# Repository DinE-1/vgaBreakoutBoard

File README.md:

# VGA Breakout

A KiCad PCB breakout board providing easy access to VGA connector pins.

# Pictures

## Front

## Back

## License

Copyright (c) 2026 DinE-1

Licensed under the CERN Open Hardware Licence Version 2 - Permissive (CERN-OHL-P v2).

See the LICENSE file for details.

## Disclaimer

This design is provided as-is, without warranty of any kind.

Verify electrical compatibility and suitability for your application before manufacture or use. DinE-1 assumes no responsibility for damage, malfunction, data loss, or other consequences resulting from use of this design.

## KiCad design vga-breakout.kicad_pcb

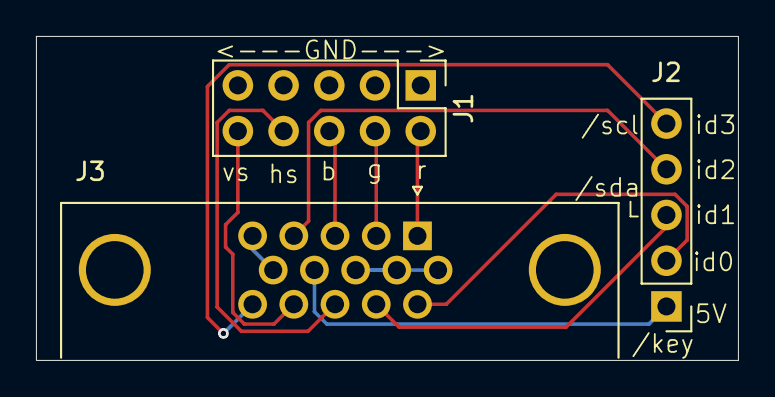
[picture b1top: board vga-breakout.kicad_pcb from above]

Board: 2 copper layers, 39.0 x 18.0 mm, 3 parts (0 on the bottom side), 11 nets.

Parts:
J1: Conn_02x05_Odd_Even; PinHeader_2x05_P2.54mm_Vertical
J2: Conn_01x05_Pin; PinHeader_1x05_P2.54mm_Vertical
J3: DE15_Socket_HighDensity_MountingHoles; DSUB-15-HD_Socket_Horizontal_P2.29x1.90mm_EdgePinOffset3.03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

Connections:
/5V/key: J2.1, J3.9
/blue: J1.6, J3.3
/green: J1.4, J3.2
/hSync: J1.8, J3.13
/id0/res: J2.2, J3.11
/id1/sda: J2.3, J3.12
/id2/res: J2.4, J3.4
/id3/scl: J2.5, J3.15
/red: J1.2, J3.1
/vSync: J1.10, J3.14
GND: J1.1, J1.3, J1.5, J1.7, J1.9, J3.5, J3.6, J3.7, J3.8, J3.10

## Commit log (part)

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2026-05-30 Initial VGA breakout board design
2026-05-30 organise export
2026-05-30 add pics
2026-05-30 remove ferrite from sheilding, rerouting
2026-05-30 less angled
2026-05-31 add tvs diode, reroute
    reroute with vias only for 5V trace
2026-06-19 silkscreen
    moving text

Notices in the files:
vga-breakout.kicad_pcb:
license: CERN-OHL-P-2.0
CERN-OHL-P-2.0
